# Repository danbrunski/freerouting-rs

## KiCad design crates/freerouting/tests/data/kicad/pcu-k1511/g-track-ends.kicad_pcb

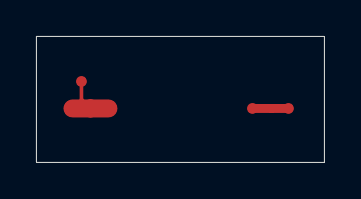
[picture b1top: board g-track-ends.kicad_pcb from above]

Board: 4 copper layers, 16.0 x 7.0 mm, 5 parts (0 on the bottom side), 2 nets.

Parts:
P1, P2, P3, P4, P5: Pad; Pad_D0.6mm

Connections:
N1: P1.1, P2.1, P3.1
N2: P4.1, P5.1

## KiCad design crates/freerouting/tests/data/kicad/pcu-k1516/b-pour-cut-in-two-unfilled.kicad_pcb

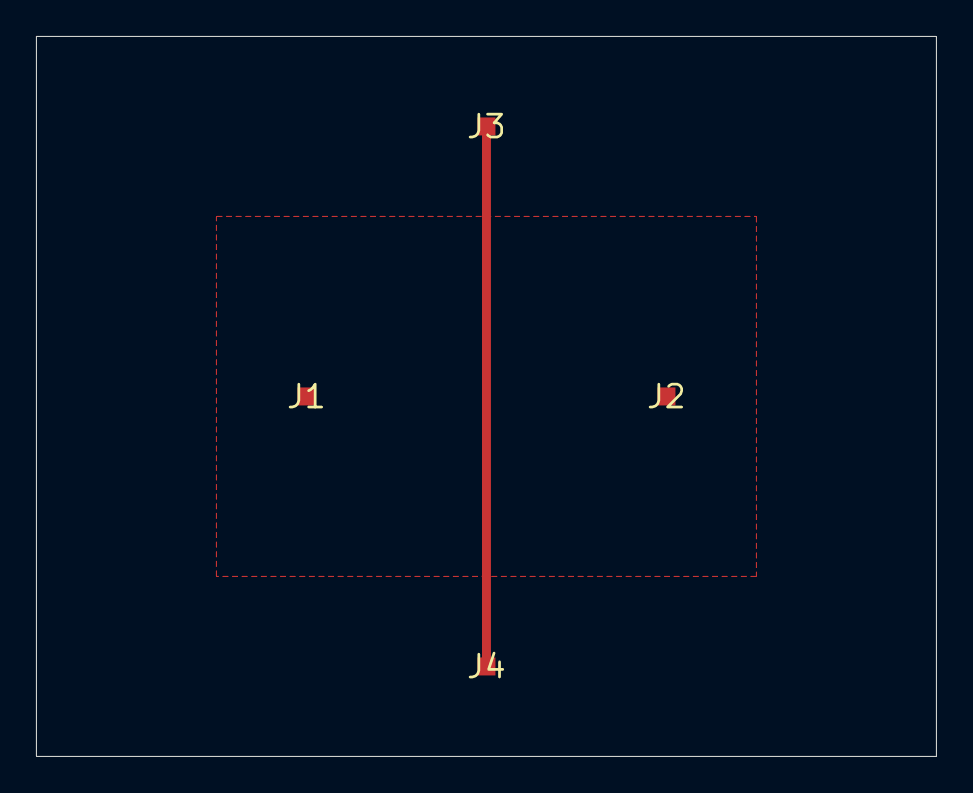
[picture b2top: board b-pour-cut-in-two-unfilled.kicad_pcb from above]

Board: 4 copper layers, 50.0 x 40.0 mm, 4 parts (0 on the bottom side), 2 nets.

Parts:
J1, J2, J3, J4: x; smd

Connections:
N1: J1.1, J2.1
N2: J3.1, J4.1
